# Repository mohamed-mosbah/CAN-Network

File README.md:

# CAN-Network
This project consists of two CAN nodes puplishing and listening to messages on a CAN bus based on an esp32.

ECU_1 is programmed to read data using SPI from an ABPDRRV015PDSA3 sensor which can read both pressure and temperature. ECU_1 converts the temperature to celsius and converts the pressure to 0.01 millibar and puplishes these two values in two different CAN frames with predefined identifiers.

ECU_2 is programmed to listen to pressure and temperature frames on the bus and prints them upon receiving.

Video Overview of the working application:

Hardware: https://youtu.be/kiKiHDHKg5g

Software: https://youtu.be/EGtzW8QNXfk

### How to compile

Install esp_idf framework: https://docs.espressif.com/projects/esp-idf/en/latest/esp32/get-started/index.html.

Open ESP-IDF CMD

Connect the esp to any USB port and do the following:
```bash
git clone https://github.com/mohamed-mosbah/CAN-Network/
cd CAN-Network/ECU_1/
idf.py set-target esp32
idf.py -p <PORT> flash monitor
```
You need to know what is the name of the port, being used. This can be known from the device manager under Ports (COM & LPT). In my case it is typically COM7 so the last command would be:
```bash
idf.py -p COM7 flash monitor
```

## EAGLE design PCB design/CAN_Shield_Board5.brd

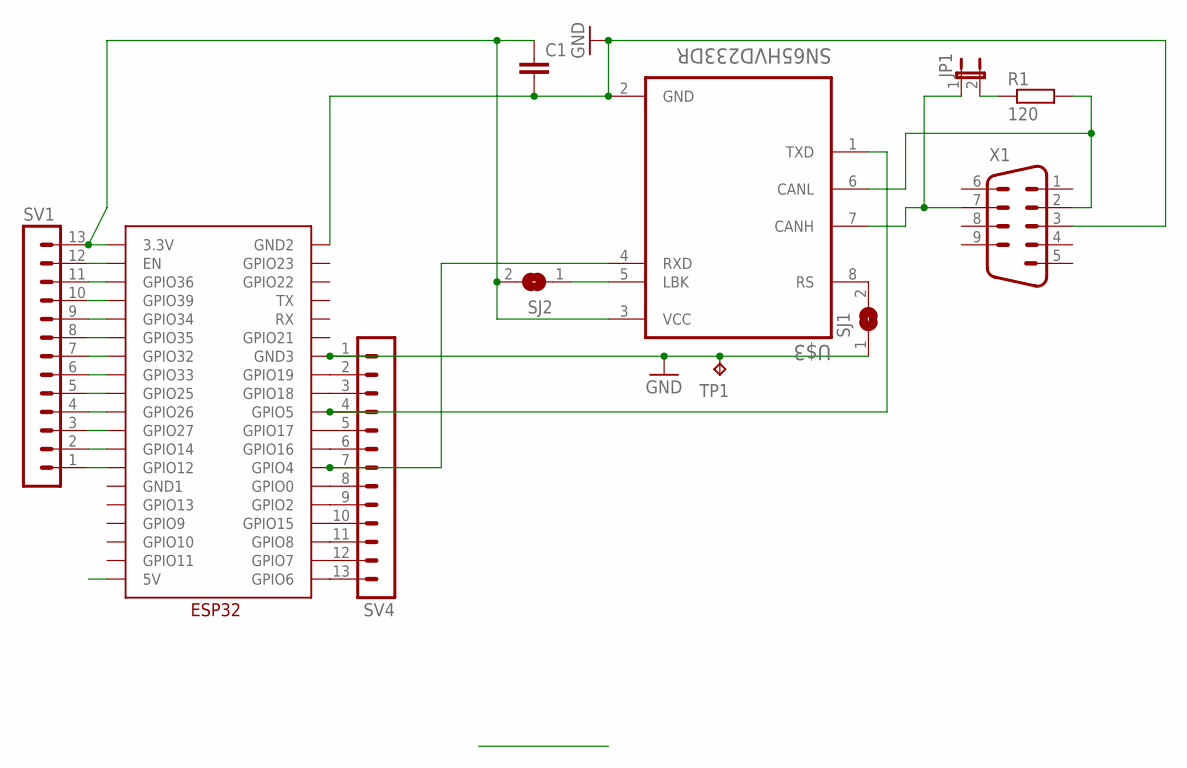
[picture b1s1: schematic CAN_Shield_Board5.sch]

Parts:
C1: C-EUC0805; C0805
JP1: JP1E; JP1
R1: 120; R0805
SJ1, SJ2: SJ
SV1, SV4: MA13-1
TP1: TPPAD1-13Y; P1-13Y
U$1: ESP32
U$3: SN65HVD233DR; SOIC127P599X175-8N
X1: M09HP

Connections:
CANHI: JP1.1, U$3.7 (CANH), X1.7
CANLO: R1.2, U$3.6 (CANL), X1.2
CANRX: SV4.7, U$1.GPIO4, U$3.4 (RXD)
CANTX: SV4.4, U$1.GPIO5, U$3.1 (TXD)
GND: C1.2, SJ1.1, SV4.1, TP1.TP, U$1.GND2, U$1.GND3, U$3.2 (GND), X1.3
unnamed: SV1.1, U$1.GPIO12
unnamed: SV1.2, U$1.GPIO14
unnamed: SV1.3, U$1.GPIO27
unnamed: SV1.4, U$1.GPIO26
unnamed: SV1.5, U$1.GPIO25
unnamed: SJ1.2, U$3.8 (RS)
unnamed: SV1.6, U$1.GPIO33
unnamed: SV1.7, U$1.GPIO32
unnamed: SV1.8, U$1.GPIO35
unnamed: SV1.9, U$1.GPIO34
unnamed: SV1.10, U$1.GPIO39
unnamed: SV1.11, U$1.GPIO36
unnamed: SJ2.1, U$3.5 (LBK)
unnamed: SV1.12, U$1.EN
unnamed: SV4.2, U$1.GPIO19
unnamed: SV4.3, U$1.GPIO18
unnamed: SV4.5, U$1.GPIO17
unnamed: SV4.6, U$1.GPIO16
unnamed: SV4.8, U$1.GPIO0
unnamed: SV4.9, U$1.GPIO2
unnamed: SV4.10, U$1.GPIO15
unnamed: JP1.2, R1.1
unnamed: SV4.11, U$1.GPIO8
unnamed: SV4.12, U$1.GPIO7
unnamed: SV4.13, U$1.GPIO6
VCC: C1.1, SJ2.2, SV1.13, U$1.3.3V, U$3.3 (VCC)

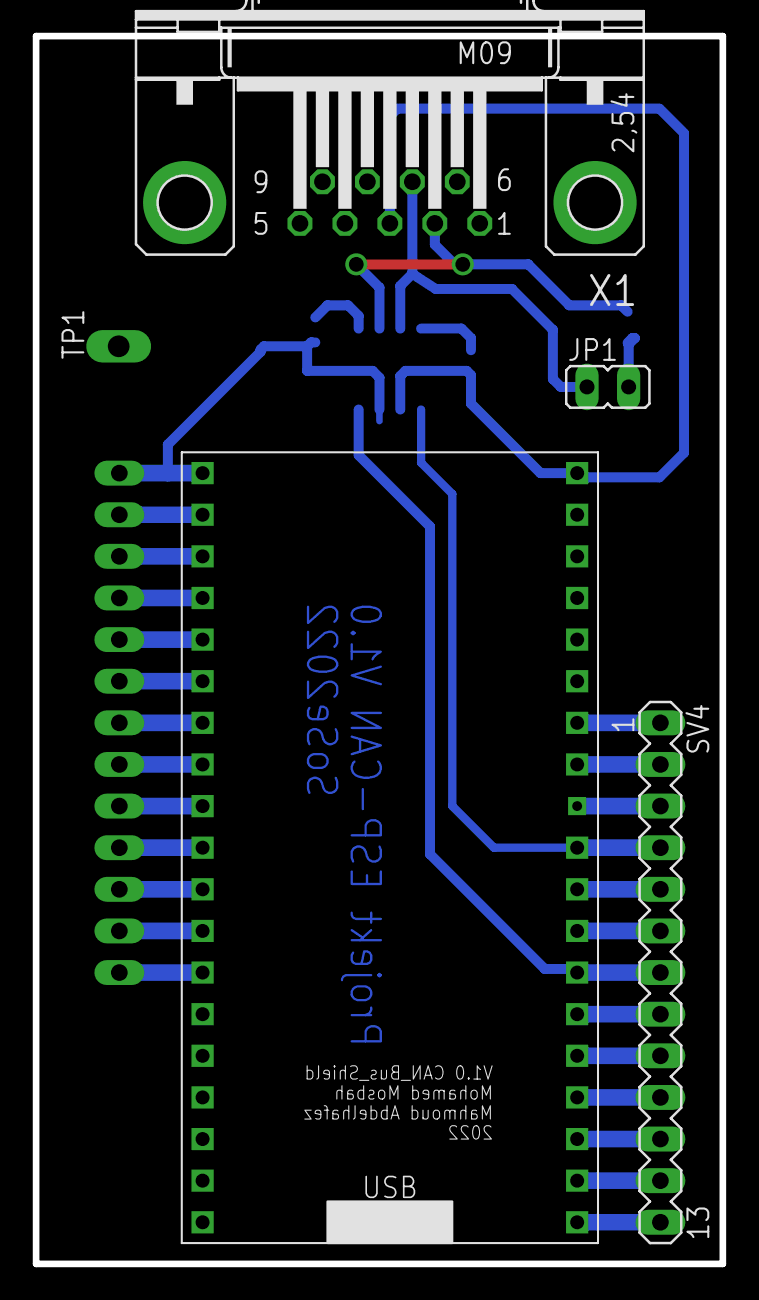
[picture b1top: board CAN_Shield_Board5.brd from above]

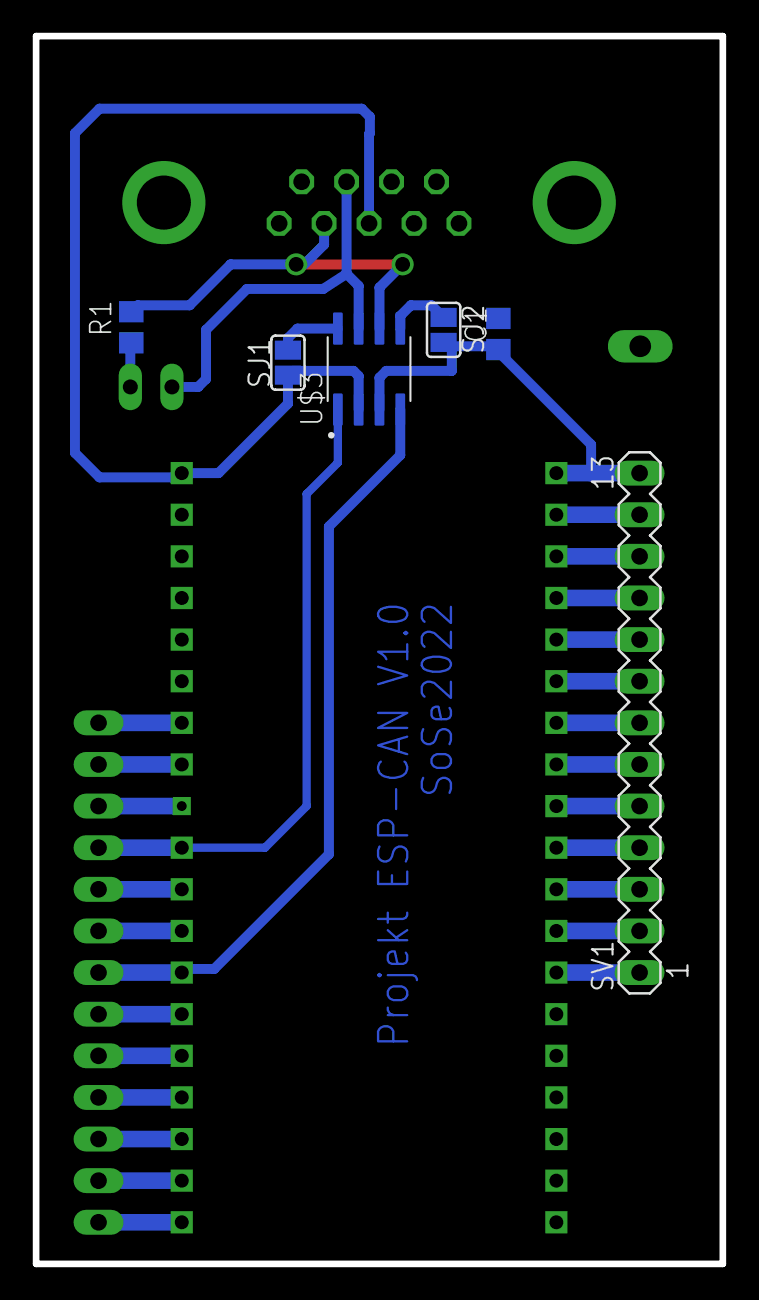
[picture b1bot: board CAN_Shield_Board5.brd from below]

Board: 2 copper layers, 41.9 x 74.9 mm, 15 parts (6 on the bottom side), 31 nets.

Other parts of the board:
U$2, U$4, U$5, U$6: PASSMARK

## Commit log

2022-07-10 Code for both ECUs
2022-07-10 added the design and the schematic
2022-07-10 updated description comment
